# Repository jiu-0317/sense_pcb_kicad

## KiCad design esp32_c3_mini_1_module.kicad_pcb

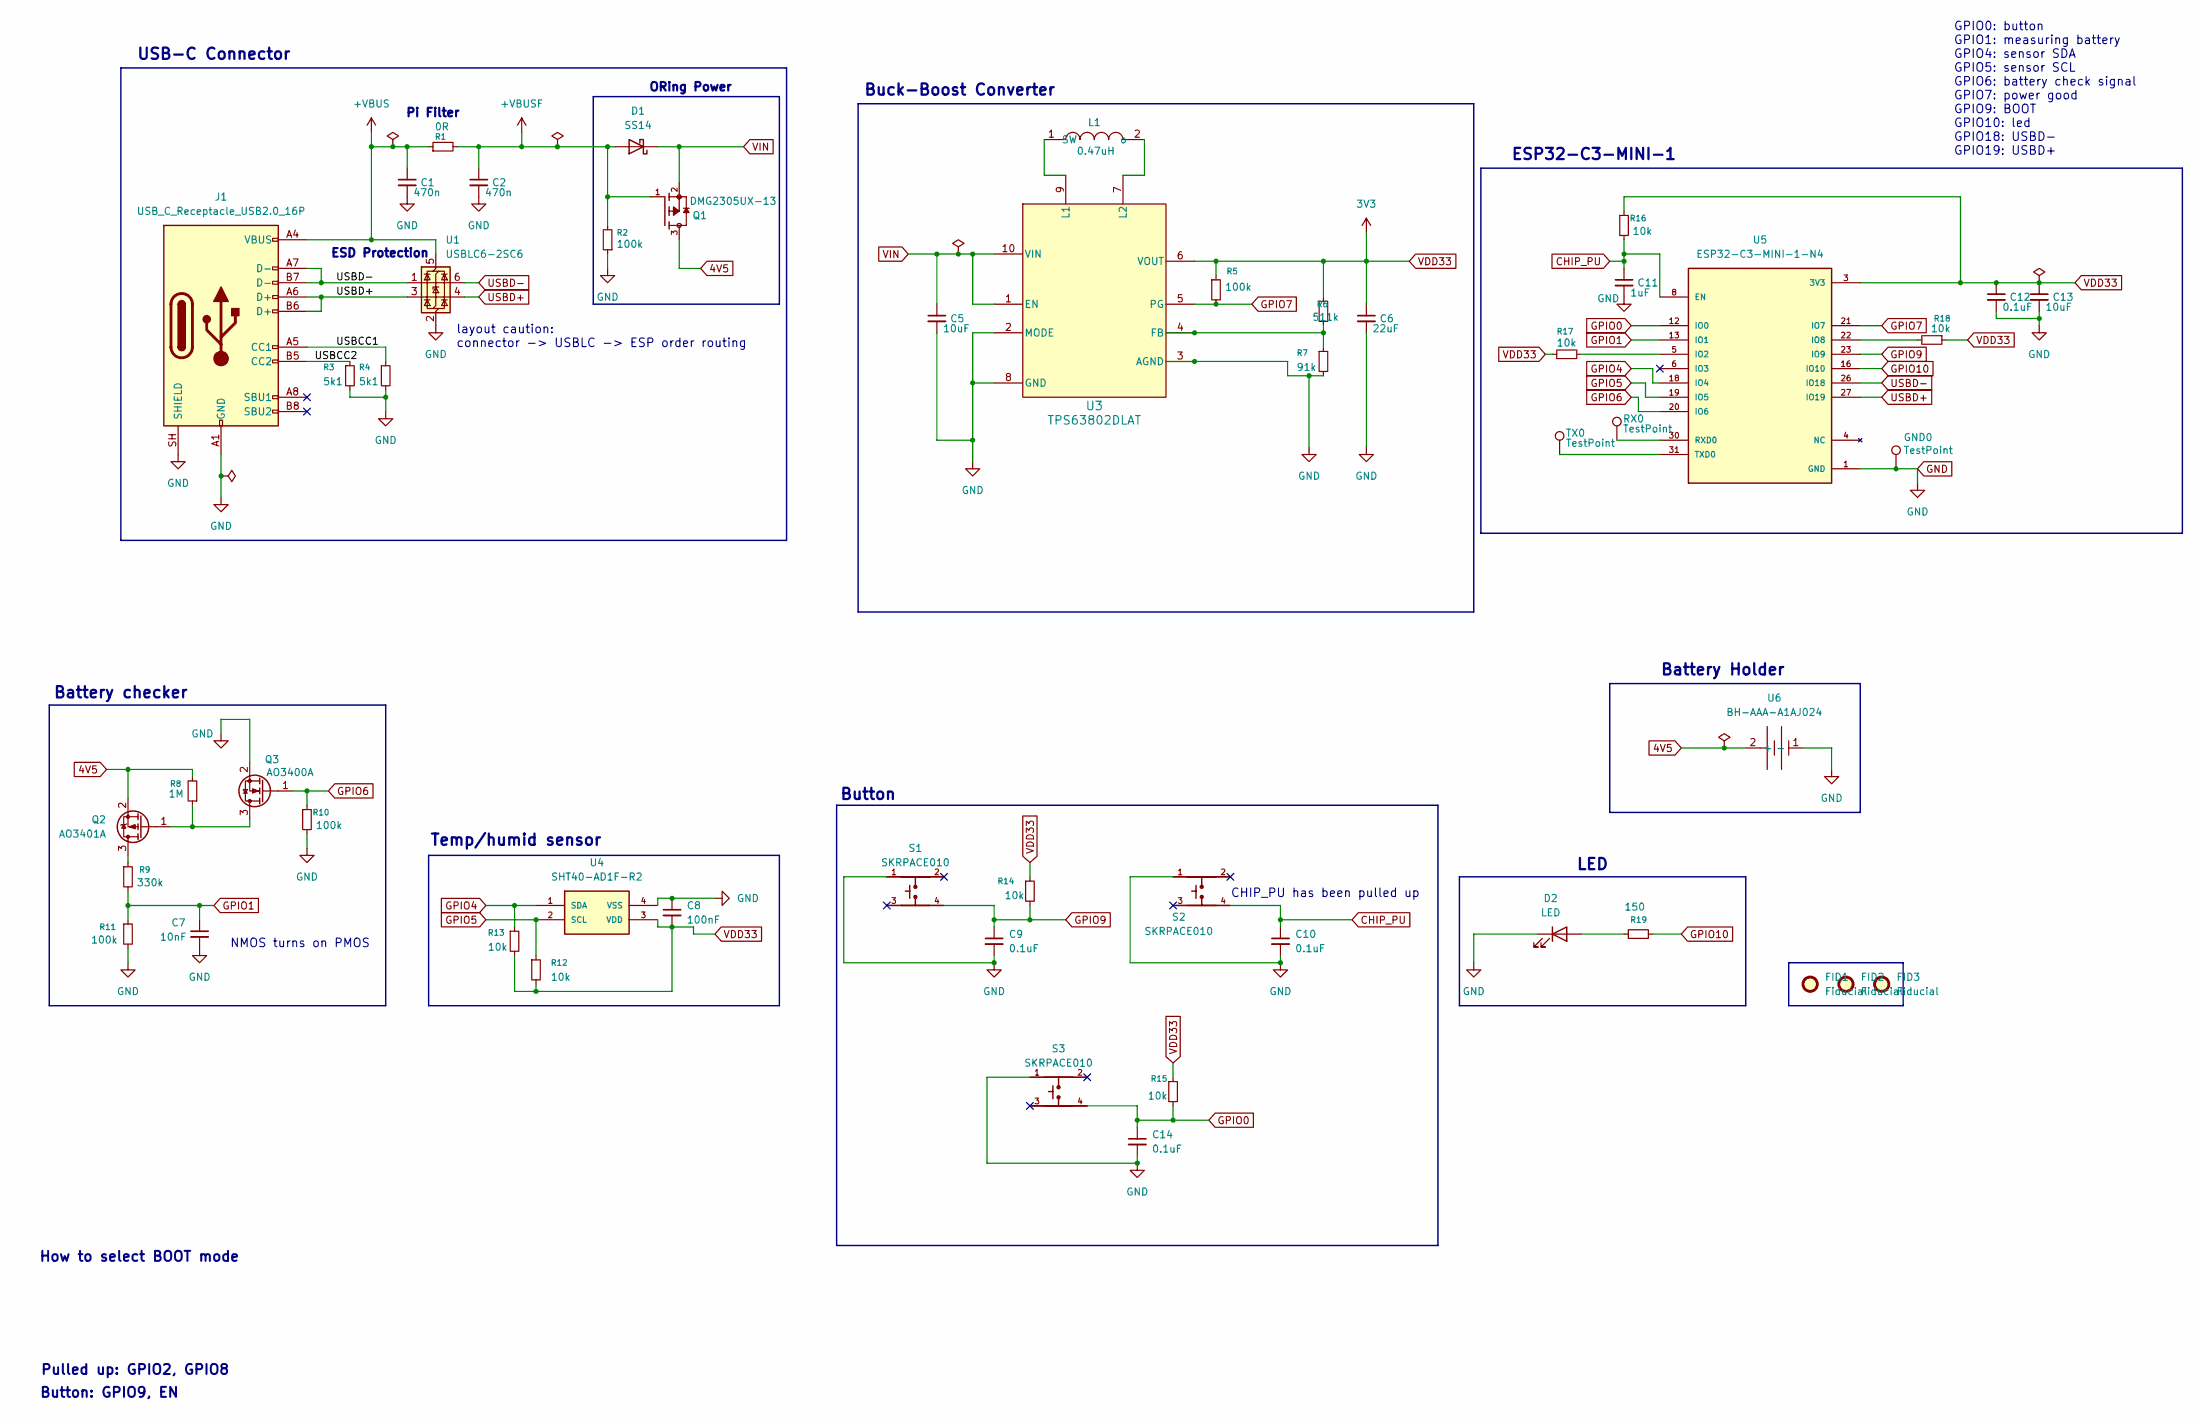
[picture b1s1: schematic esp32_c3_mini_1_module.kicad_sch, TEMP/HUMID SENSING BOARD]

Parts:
C1, C2: 470n; CAPC2012X95N; MF_part_number CL21B105KBFNNNE; LCSC C28323
C5: 10uF; CAPC2012X95N; MF_part_number CL21B105KBFNNNE; LCSC C28323
C6: 22uF; CAPC2012X95N; MF_part_number CL21B105KBFNNNE; LCSC C28323
C7: 10nF; CAPC2012X95N; MF_part_number CL21B103KBANNNC; LCSC C1710
C8: 100nF; CAPC2012X95N; MF_part_number CC0805KRX7R6BB104; LCSC C1852967
C9, C10, C12, C14: 0.1uF; CAPC2012X95N; MF_part_number CC0805KRX7R6BB104; LCSC C1852967
C11: 1uF; CAPC2012X95N; MF_part_number CL21B105KBFNNNE; LCSC C28323
C13: 10uF; CAPC2012X95N; MF_part_number CL21A106KPFNNNE; LCSC C17024
D1: SS14; D_SMA; MF_part_number SS14-E3/61T; LCSC C47460
D2: LED; XL-3528SURC; MF_part_number XL-3528SURC; LCSC C2843800
FID1, FID2, FID3: Fiducial; Fiducial_1mm_Mask2mm
GND0: TestPoint; TestPoint_Pad_D1.5mm
J1: USB_C_Receptacle_USB2.0_16P; USB_C_Receptacle_GCT_USB4105-xx-A_16P_TopMnt_Horizontal; MF_part_number USB4105-GF-A-060; LCSC C3025063
L1: 0.47uH; xfl4015_inductor; MF_part_number XFL4015-471MEC; LCSC C18221164
Q1: DMG2305UX-13; MPN DMG2305UX-13; LCSC C144153
Q2: AO3401A; SOT-23; MF_part_number AO3401A; LCSC C15127
Q3: AO3400A; SOT-23
R1: 0R; RESC2012X60N; MF_part_number RC0805FR-0710KL; LCSC C84376
R2: 100k; RESC2012X60N; MF_part_number RC0805FR-0710KL; LCSC C84376
R3, R4: 5k1; RESC2012X60N; MF_part_number RC0805FR-0710KL; LCSC C84376
R5, R10, R11: 100k; RESC2012X60N; MF_part_number RC0805FR-07100KL; LCSC C96346
R6: 511k; RESC2012X60N; MF_part_number RC0805FR-0710KL; LCSC C84376
R7: 91k; RESC2012X60N; MF_part_number RC0805FR-0710KL; LCSC C84376
R8: 1M; RESC2012X60N; MF_part_number RC0805FR-071ML; LCSC C107700
R9: 330k; RESC2012X60N; MF_part_number RC0805FR-07330KL; LCSC C114528
R12, R13, R14, R15, R16, R17, R18: 10k; RESC2012X60N; MF_part_number RC0805FR-0710KL; LCSC C84376
R19: 150; RESC2012X60N; MF_part_number RC0805FR-07150RL; LCSC C114523
RX0: TestPoint; TestPoint_Pad_D1.5mm
S1, S2, S3: SKRPACE010; SW_SKRPACE010; MF_part_number SKRPACE010; LCSC C139797
TX0: TestPoint; TestPoint_Pad_D1.5mm
U1: USBLC6-2SC6; SOT-23-6; MF_part_number USBLC6-2SC6; LCSC C7519
U3: TPS63802DLAT; MF_part_number TPS63802DLAT; LCSC C1849531
U4: SHT40-AD1F-R2; SHT4X; MF_part_number SHT40-AD1F-R2; LCSC C7461846
U5: ESP32-C3-MINI-1-N4; XCVR_ESP32-C3-MINI-1-N4; PARTREV v1.0; LCSC C2838502
U6: BH-AAA-A1AJ024; BAT-TH_BH-AAA-A1AJ024; MPN BH-AAA-A1AJ024; LCSC Part C5290193

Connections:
4V5: Q1.3, Q2.2 (S), R8.2, U6.2 (+)
+VBUS: C1.1, J1.A4 (VBUS), J1.A9 (VBUS), J1.B4 (VBUS), J1.B9 (VBUS), R1.1, U1.5 (VBUS)
+VBUSF: C2.1, D1.2 (A), Q1.1, R1.2, R2.2
/USBCC1: J1.A5 (CC1), R4.1
/USBCC2: J1.B5 (CC2), R3.1
CHIP_PU: C10.1, C11.1, R16.2, S2.4, U5.8 (EN)
GND: C1.2, C2.2, C5.2, C6.2, C7.2, C8.1, C9.2, C10.2, C11.2, C12.2, C13.2, C14.2, D2.1 (K), GND0.1 (1_1), J1.A1 (GND), J1.A12 (GND), J1.B1 (GND), J1.B12 (GND), J1.SH (SHIELD), Q3.2 (S), R2.1, R3.2, R4.2, R7.2, R10.2, R11.2, S1.1, S2.1, S3.1, U1.2 (GND), U3.2 (MODE), U3.3 (AGND), U3.8 (GND), U4.4 (VSS), U5.1 (GND), U5.2 (GND), U5.11 (GND), U5.14 (GND), U5.36 (GND), U5.37 (GND), U5.38 (GND), U5.39 (GND), U5.40 (GND), U5.41 (GND), U5.42 (GND), U5.43 (GND), U5.44 (GND), U5.45 (GND), U5.46 (GND), U5.47 (GND), U5.48 (GND), U5.49_1 (GND), U5.49_2 (GND), U5.49_3 (GND), U5.49_4 (GND), U5.49_5 (GND), U5.49_6 (GND), U5.49_7 (GND), U5.49_8 (GND), U5.49_9 (GND), U5.50 (GND), U5.51 (GND), U5.52 (GND), U5.53 (GND), U6.1 (-)
GPIO0: C14.1, R15.2, S3.4, U5.12 (IO0)
GPIO1: C7.1, R9.2, R11.1, U5.13 (IO1)
GPIO4: R13.1, U4.1 (SDA), U5.18 (IO4)
GPIO5: R12.1, U4.2 (SCL), U5.19 (IO5)
GPIO6: Q3.1 (G), R10.1, U5.20 (IO6)
GPIO7: R5.2, U3.5 (PG), U5.21 (IO7)
GPIO9: C9.1, R14.2, S1.4, U5.23 (IO9)
GPIO10: R19.2, U5.16 (IO10)
unnamed: D2.2 (A), R19.1
unnamed: L1.1 (SW), U3.9 (L1)
unnamed: L1.2 (o), U3.7 (L2)
unnamed: Q2.3 (D), R9.1
unnamed: Q2.1 (G), Q3.3 (D), R8.1
unnamed: R6.2, R7.1, U3.4 (FB)
unnamed: R17.2, U5.5 (IO2)
unnamed: R18.2, U5.22 (IO8)
unnamed: RX0.1 (1_1), U5.30 (RXD0)
unnamed: TX0.1 (1_1), U5.31 (TXD0)
USBD+: J1.A6 (D+), J1.B6 (D+), U1.3 (I/O2), U1.4 (I/O2), U5.27 (IO19)
USBD-: J1.A7 (D-), J1.B7 (D-), U1.1 (I/O1), U1.6 (I/O1), U5.26 (IO18)
VDD33: C6.1, C8.2, C12.1, C13.1, R5.1, R6.1, R12.2, R13.2, R14.1, R15.1, R16.1, R17.1, R18.1, U3.6 (VOUT), U4.3 (VDD), U5.3 (3V3)
VIN: C5.1, D1.1 (K), Q1.2, U3.1 (EN), U3.10 (VIN)

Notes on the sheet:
LED
Button: GPIO9, EN
GPIO0: button GPIO1: measuring battery GPIO4: sensor SDA GPIO5: sensor SCL GPIO6: battery check signal GPIO7: power good GPIO9: BOOT GPIO10: led GPIO18: USBD- GPIO19: USBD+
Pulled up: GPIO2, GPIO8
Pi Filter
ORing Power
Battery Holder
Buck-Boost Converter
USB-C Connector
ESP32-C3-MINI-1
layout caution: connector -> USBLC -> ESP order routing
Battery checker
Temp/humid sensor
NMOS turns on PMOS
Button
CHIP_PU has been pulled up
How to select BOOT mode
ESD Protection

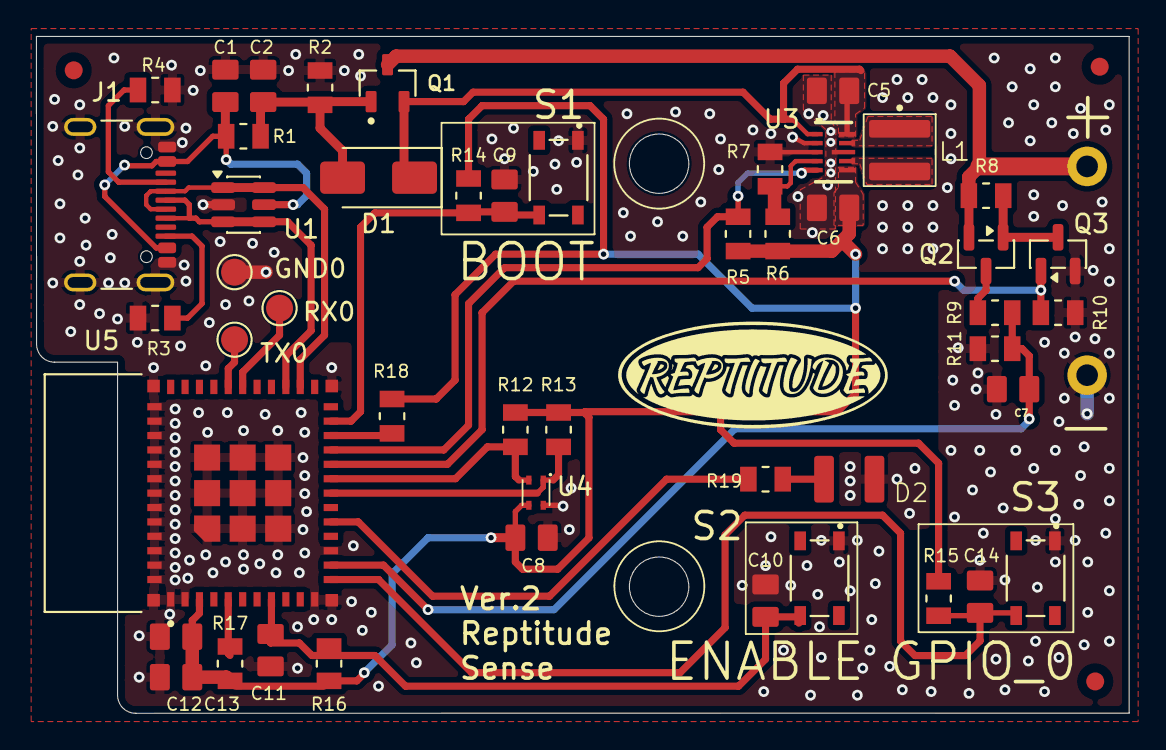
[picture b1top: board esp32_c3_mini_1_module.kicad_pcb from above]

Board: 2 copper layers, 60.7 x 37.6 mm, 52 parts (1 on the bottom side), 29 nets.

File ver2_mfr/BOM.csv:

"Reference","Qty","Value","DNP","Exclude from BOM","Exclude from Board","Footprint","Datasheet","Description_1","MANUFACTURER","MF_part_number","Package","LCSC"
"C5,C13","2","10uF","","","","Custom:CAPC2012X95N","https://www.lcsc.com/datasheet/C17024.pdf,https://www.lcsc.com/datasheet/C28323.pdf","10uF ±10% 10V Ceramic Capacitor X5R 0805,1uF ±10% 50V Ceramic Capacitor X7R 0805","Samsung Electro-Mechanics","CL21A106KPFNNNE,CL21B105KBFNNNE","0805","C17024,C28323"
"R2,R5,R10","3","100k","","","","Custom:RESC2012X60N","https://www.lcsc.com/datasheet/C84376.pdf,https://www.lcsc.com/datasheet/C96346.pdf","125mW 100kΩ 150V Thick Film Resistor ±100ppm/℃ ±1% 0805 Chip Resistor - Surface Mount RoHS,125mW 10kΩ 150V Thick Film Resistor ±100ppm/℃ ±1% 0805 Chip Resistor - Surface Mount RoHS","YAGEO","RC0805FR-07100KL,RC0805FR-0710KL","0805","C84376,C96346"
"C7","1","10nF","","","","Custom:CAPC2012X95N","https://www.lcsc.com/datasheet/C1710.pdf","10nF ±10% 50V Ceramic Capacitor X7R 0805","Samsung Electro-Mechanics","CL21B103KBANNNC","0805","C1710"
"U1","1","USBLC6-2SC6","","","","Package_TO_SOT_SMD:SOT-23-6","https://www.st.com/resource/en/datasheet/usblc6-2.pdf","ESD DIODE 5.25VWM 17VC SOT-23-6L","ST","USBLC6-2SC6","SOT-23-6L","C7519"
"Q2","1","AO3401A","","","","Package_TO_SOT_SMD:SOT-23","http://www.aosmd.com/pdfs/datasheet/AO3401A.pdf","30V 4A Surface Mount SOT-23","AOS","AO3401A","SOT-23","C15127"
"C1,C2,C3,C4","4","470n","","","","Custom:CAPC2012X95N","https://www.lcsc.com/datasheet/C28323.pdf","1uF ±10% 50V Ceramic Capacitor X7R 0805","Samsung Electro-Mechanics","CL21B105KBFNNNE","0805","C28323"
"C6","1","22uF","","","","Custom:CAPC2012X95N","https://www.lcsc.com/datasheet/C28323.pdf","1uF ±10% 50V Ceramic Capacitor X7R 0805","Samsung Electro-Mechanics","CL21B105KBFNNNE","0805","C28323"
"C11","1","1uF","","","","Custom:CAPC2012X95N","https://www.lcsc.com/datasheet/C28323.pdf","1uF ±10% 50V Ceramic Capacitor X7R 0805","Samsung Electro-Mechanics","CL21B105KBFNNNE","0805","C28323"
"D1","1","SS14","","","","Diode_SMD:D_SMA","https://www.vishay.com/docs/88746/ss12.pdf","DIODE SCHOTTKY 40V SMA(DO-214AC)","VISHAY","SS14-E3/61T","SMA(DO-214AC)","C47460"
"R1","1","0R","","","","Custom:RESC2012X60N","https://www.lcsc.com/datasheet/C84376.pdf","125mW 10kΩ 150V Thick Film Resistor ±100ppm/℃ ±1% 0805 Chip Resistor - Surface Mount RoHS","YAGEO","RC0805FR-0710KL","0805","C84376"
"R3,R4","2","5k1","","","","Custom:RESC2012X60N","https://www.lcsc.com/datasheet/C84376.pdf","125mW 10kΩ 150V Thick Film Resistor ±100ppm/℃ ±1% 0805 Chip Resistor - Surface Mount RoHS","YAGEO","RC0805FR-0710KL","0805","C84376"
"R6","1","511k","","","","Custom:RESC2012X60N","https://www.lcsc.com/datasheet/C84376.pdf","125mW 10kΩ 150V Thick Film Resistor ±100ppm/℃ ±1% 0805 Chip Resistor - Surface Mount RoHS","YAGEO","RC0805FR-0710KL","0805","C84376"
"R7","1","91k","","","","Custom:RESC2012X60N","https://www.lcsc.com/datasheet/C84376.pdf","125mW 10kΩ 150V Thick Film Resistor ±100ppm/℃ ±1% 0805 Chip Resistor - Surface Mount RoHS","YAGEO","RC0805FR-0710KL","0805","C84376"
"R11,R12,R13,R14,R16,R17,R18,R19","8","10k","","","","Custom:RESC2012X60N","https://www.lcsc.com/datasheet/C84376.pdf","125mW 10kΩ 150V Thick Film Resistor ±100ppm/℃ ±1% 0805 Chip Resistor - Surface Mount RoHS","YAGEO","RC0805FR-0710KL","0805","C84376"
"U2","1","CH340E","","","","Package_SO:MSOP-10_3x3mm_P0.5mm","https://www.mpja.com/download/35227cpdata.pdf","USB to Serial Port Chip CH340","WCH","CH340E","MSOP-10","C99652"
"R8","1","1M","","","","Custom:RESC2012X60N","https://www.lcsc.com/datasheet/C107700.pdf","125mW 1MΩ 150V Thick Film Resistor ±100ppm/℃ ±1% 0805 Chip Resistor - Surface Mount RoHS","YAGEO","RC0805FR-071ML","0805","C107700"
"R15","1","150","","","","Custom:RESC2012X60N","https://www.lcsc.com/datasheet/C114523.pdf","150Ω 125mW 150V Thick Film Resistor ±100ppm/℃ ±1% 0805 Chip Resistor - Surface Mount RoHS","YAGEO","RC0805FR-07150RL","0805","C114523"
"R9","1","330k","","","","Custom:RESC2012X60N","https://www.lcsc.com/datasheet/C114528.pdf","125mW 330kΩ 150V Thick Film Resistor ±100ppm/℃ ±1% 0805 Chip Resistor - Surface Mount RoHS","YAGEO","RC0805FR-07330KL","0805","C114528"
"S1,S2,S3","3","SKRPACE010","","","","Custom:SW_SKRPACE010","https://www.lcsc.com/datasheet/C139797.pdf","Switch Tactile N.O. SPST Button J-Bend 0.05A 16VDC 2.55N SMD Automotive T/R","ALPSALPINE","SKRPACE010","SMD-4P,4.2x3.2mm","C139797"
"Q1","1","DMG2305UX-13","","","","Custom:DMG2305UX-13","https://s3.amazonaws.com/snapeda/datasheet/DMG2305UX-13_Diod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","MOSFET P-CH 20V 5A SOT-23","Diodes Inc.","DMG2305UX-13","SOT-23","C144153"
"U3","1","TPS63802DLAT","","","","Custom:TPS63802DLAT","https://www.ti.com/lit/gpn/tps63802","High-efficiency, low-IQ step-down/step-up converter in DFN package","TI","TPS63802DLAT","VSON-10(2x3)","C1849531"
"C8","1","100nF","","","","Custom:CAPC2012X95N","https://www.lcsc.com/datasheet/C1852967.pdf","100nF ±10% 10V Ceramic Capacitor X7R 0805","YAGEO","CC0805KRX7R6BB104","0805","C1852967"
"C9,C10,C12,C14","4","0.1uF","","","","Custom:CAPC2012X95N","https://www.lcsc.com/datasheet/C1852967.pdf","100nF ±10% 10V Ceramic Capacitor X7R 0805","YAGEO","CC0805KRX7R6BB104","0805","C1852967"
"U5","1","ESP32-C3-MINI-1-N4","","","","Custom:XCVR_ESP32-C3-MINI-1-N4","https://www.lcsc.com/datasheet/C2838502.pdf","Transceiver On-board PCB Antenna -98dBm SMD,16.6x13.2mm RF Transceiver Modules and Modems RoHS","Espressif Systems","ESP32-C3-MINI-1-N4","SMD,16.6x13.2mm","C2838502"
"D2","1","LED","","","","Custom:XL-3528SURC","https://www.lcsc.com/datasheet/C2843800.pdf?spm=wm.sxq.inf.g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","LED RED WATER CLEAR SMD","XINGLIGHT","XL-3528SURC","SMD3528-2P","C2843800"
"J1","1","USB_C_Receptacle_USB2.0_16P","","","","Connector_USB:USB_C_Receptacle_GCT_USB4105-xx-A_16P_TopMnt_Horizontal","https://www.usb.org/sites/default/files/documents/usb_type-c.zip","USB Type C Receptacle for USB 2.0, SMT Type, PCB Top Mount","Global Connector Technology","USB4105-GF-A-060","SMD","C3025063"
"U6","1","BH-AAA-A1AJ024","","","","Custom:BAT-TH_BH-AAA-A1AJ024","https://www.lcsc.com/datasheet/C5290193.pdf","BATTERY HOLDER CYLINDRICAL AAA","MYOUNG","BH-AAA-A1AJ024","-","C5290193"
"U4","1","SHT40-AD1F-R2","","","","Custom:SHT4X","https://jlcpcb.com/api/file/downloadByFileSystemAccessId/859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","-40℃~+125℃ 0%RH~100%RH 1.08V~3.6V 16bit 400nA I2C ±0.2℃ ±1.8%RH DFN-4(1.5x1.5) Temperature and Humidity Sensor ROHS ","Sensirion"," SHT40-AD1F-R2","DFN-4(1.5x1.5) ","C7461846"
"L1","1","0.47uH","","","","Custom:xfl4015_inductor","https://www.coilcraft.com/getmedia/84927b8b-f089-421b-a7f4-a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","FIXED IND 470nH SMD,4x4mm","Coilcraft","XFL4015-471MEC","SMD,4x4mm","C18221164"
